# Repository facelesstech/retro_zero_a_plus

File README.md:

Blog post - https://facelesstech.wordpress.com/2019/10/12/arduboy-with-removable-flash-cart/
Youtube - https://youtu.be/ISeOyM-dqaA

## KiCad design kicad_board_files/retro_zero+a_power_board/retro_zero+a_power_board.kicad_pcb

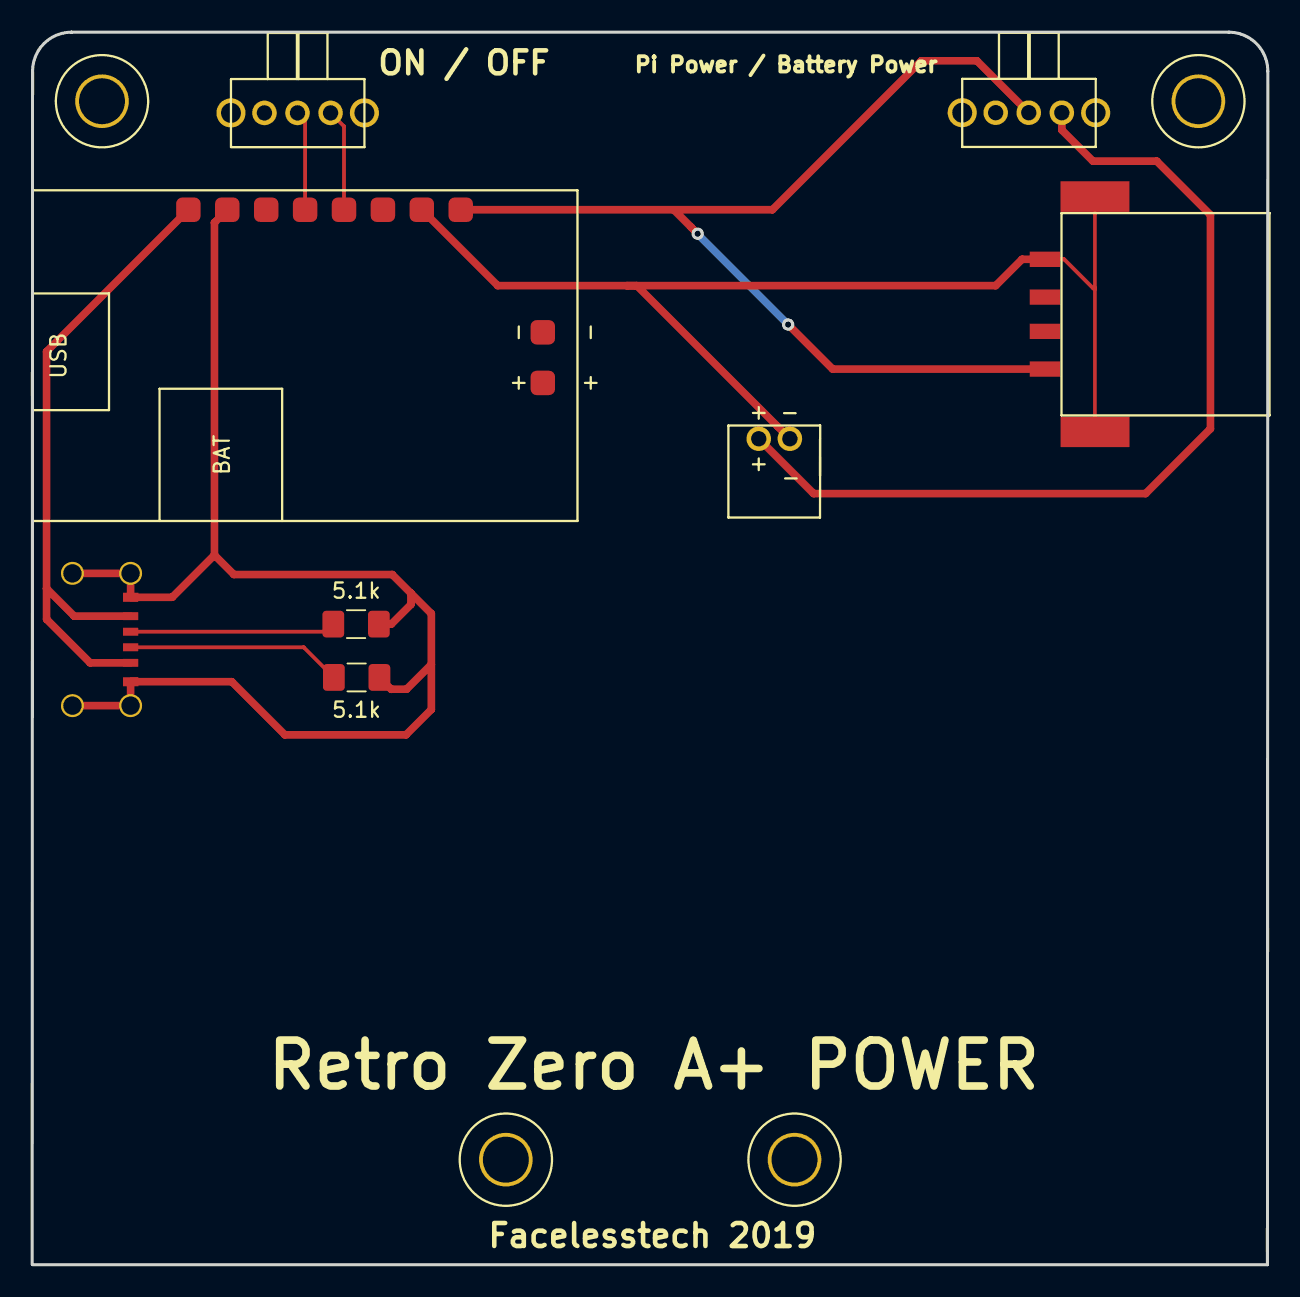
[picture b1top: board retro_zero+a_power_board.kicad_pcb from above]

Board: 2 copper layers, 80.7 x 80.5 mm, 12 parts (0 on the bottom side), 9 nets.

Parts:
5.1k, 5.1k#2: R; R_1206_3216Metric_Pad1.42x1.75mm_HandSolder
J1: USB_A; female_usb_custom_smd
SW1, SW2: SW_Push_SPDT; 3_pin_switch__right_angle_custom
U1: battery_custom; jst_2pin_right_angle
U2: power_boost_500; power_boost_500_smd
U3: usb_c_6pin; USB_C_6PIN_custom
U5, U6, U7, U8: m3_standsoffs; m3_hole_custom

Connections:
unnamed: J1.1, SW1.2, U2.8
unnamed: J1.4, J1.5, U1.1, U2.7
unnamed: 5.1k.1, 5.1k#2.1, U2.2, U3.1
unnamed: 5.1k.2, U3.3
unnamed: 5.1k#2.2, U3.4
unnamed: SW1.3, U1.2
unnamed: SW2.2, U2.4
unnamed: SW2.3, U2.5
unnamed: U2.1, U3.2

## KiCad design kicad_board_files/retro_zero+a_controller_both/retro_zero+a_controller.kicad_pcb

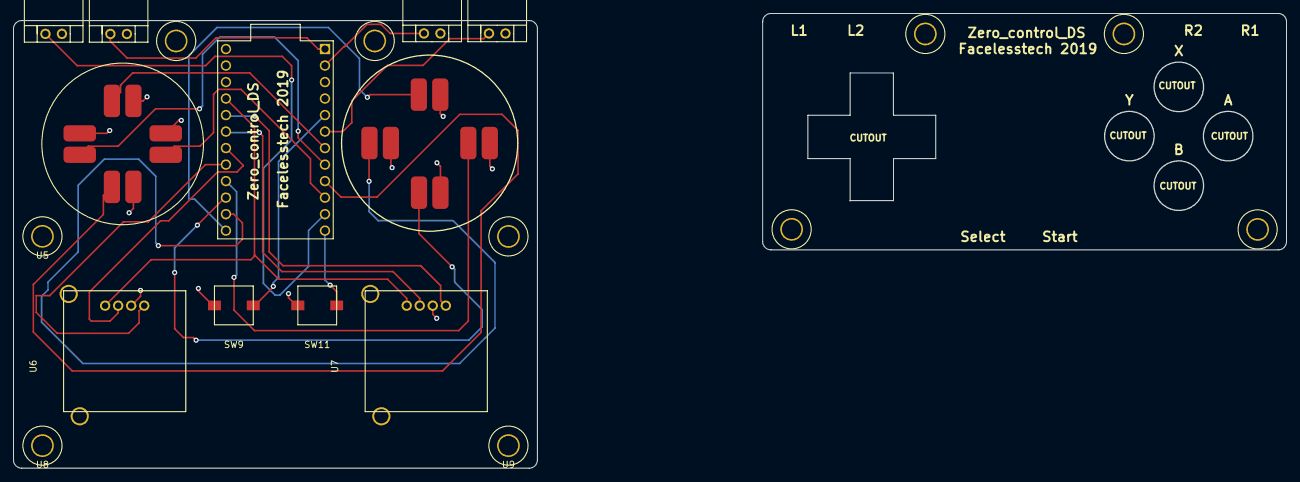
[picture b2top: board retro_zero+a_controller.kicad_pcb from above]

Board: 2 copper layers, 195.8 x 69.9 mm, 27 parts (1 on the bottom side), 24 nets.

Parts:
SW1, SW2, SW3, SW4, SW5, SW6, SW7, SW8: SW_Push; gbc_buttons_custom
SW9, SW11: SW_Push; smd_soft_custom
SW10, SW12, SW13, SW14: SW_Push; right_angle_2_pin
U1: ProMicro
U2, U2#2, U3, U3#2, U4, U4#2, U5, U5#2, U8, U9: m3_standsoffs; m3_hole_custom
U6, U7: psp_under_pad_custom

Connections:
unnamed: SW1.1, U1.8
unnamed: SW1.2, SW2.2, SW3.2, SW4.2, SW5.2, SW6.2, SW7.2, SW8.2, SW9.2, SW10.2, SW11.2, SW12.2, SW13.2, SW14.2, U1.23, U6.2, U7.2
unnamed: SW2.1, U1.10
unnamed: SW3.1, U1.7
unnamed: SW4.1, U1.9
unnamed: SW5.1, U1.13
unnamed: SW6.1, U1.15
unnamed: SW7.1, U1.14
unnamed: SW8.1, U1.16
unnamed: SW9.1, U1.5
unnamed: SW10.1, U1.11
unnamed: SW11.1, U1.12
unnamed: SW12.1, U1.6
unnamed: SW13.1, U1.1
unnamed: SW14.1, U1.2
unnamed: U1.17, U6.1
unnamed: U1.18, U6.3
unnamed: U1.19, U7.3
unnamed: U1.20, U7.1
unnamed: U1.21, U6.4, U7.4
unnamed: U2.1, U2#2.1
unnamed: U3.1, U3#2.1
unnamed: U4.1, U4#2.1
unnamed: U5.1, U5#2.1

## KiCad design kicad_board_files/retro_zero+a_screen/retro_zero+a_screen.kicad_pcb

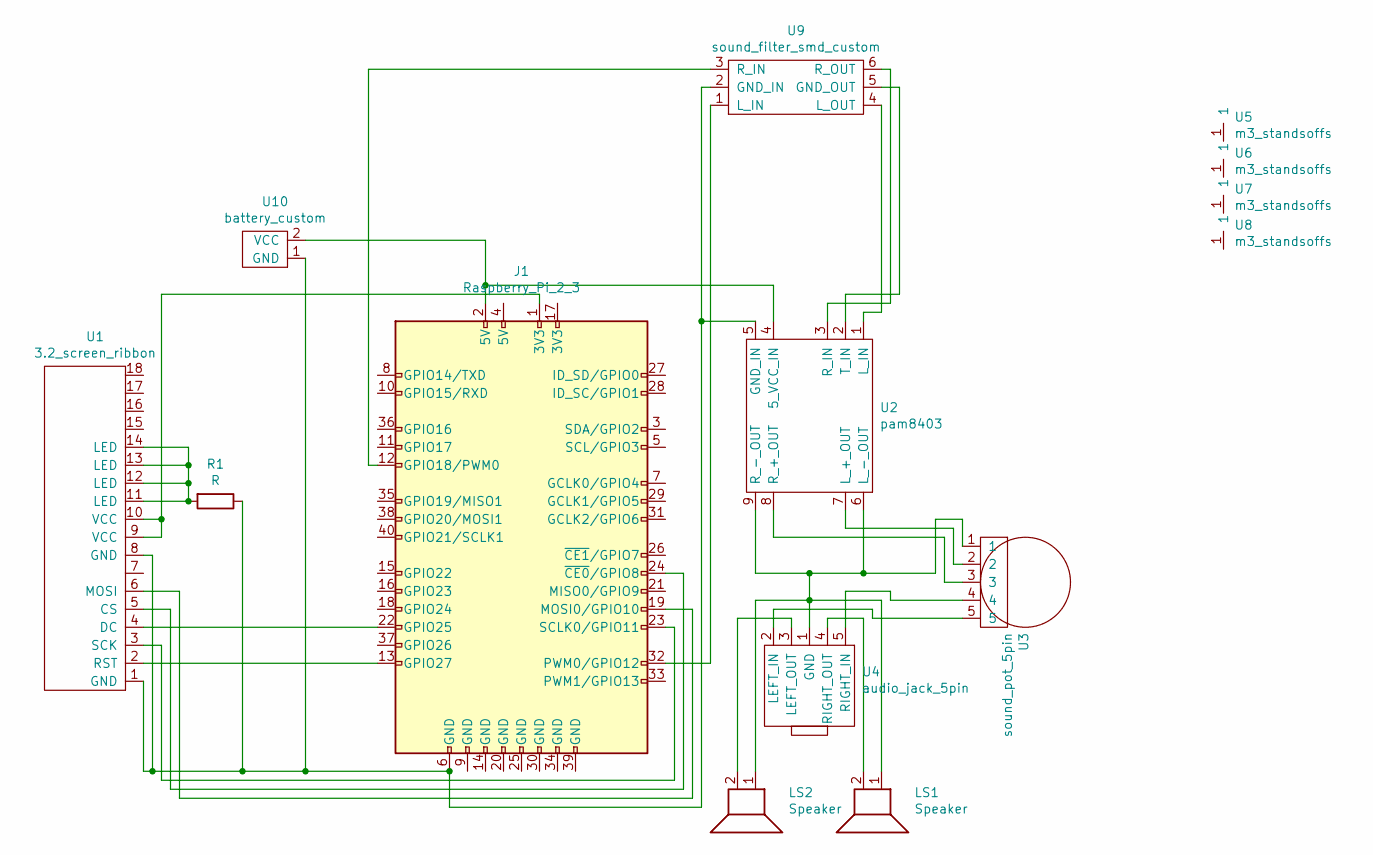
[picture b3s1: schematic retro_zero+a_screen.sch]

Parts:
J1: Raspberry_Pi_2_3; raspberry_pi_a+_gpio_smd_socket_outline_custom
LS1, LS2: Speaker; square_smd_speaker_custom
R1: R; R_1206_3216Metric
U1: 3.2_screen_ribbon; 3.2_screen_ribbon_breakout
U2: pam8403; PAM8403_custom_smd
U3: sound_pot_5pin; GBC_pot_custom
U4: audio_jack_5pin; 5_pin_3.5_jack
U5, U6, U7, U8: m3_standsoffs; m3_hole_custom
U9: sound_filter_smd_custom; Sound_filter_custom_smd
U10: battery_custom; jst_2pin_right_angle

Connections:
unnamed: J1.1 (3V3), U1.9 (VCC), U1.10 (VCC)
unnamed: J1.2 (5V), U2.4 (5_VCC_IN), U10.2 (VCC)
unnamed: J1.6 (GND), R1.1, U1.1 (GND), U1.8 (GND), U2.5 (GND_IN), U9.2 (GND_IN), U10.1 (GND)
unnamed: J1.12 (GPIO18/PWM0), U9.3 (R_IN)
unnamed: J1.13 (GPIO27), U1.2 (RST)
unnamed: J1.19 (MOSI0/GPIO10), U1.6 (MOSI)
unnamed: J1.22 (GPIO25), U1.4 (DC)
unnamed: J1.23 (SCLK0/GPIO11), U1.3 (SCK)
unnamed: J1.24 (~CE0~/GPIO8), U1.5 (CS)
unnamed: J1.32 (PWM0/GPIO12), U9.1 (L_IN)
unnamed: LS1.1, LS2.1, U2.6 (L_-_OUT), U2.9 (R_-_OUT), U3.1, U4.1 (GND)
unnamed: LS1.2, U4.4 (RIGHT_OUT)
unnamed: LS2.2, U4.3 (LEFT_OUT)
unnamed: R1.2, U1.11 (LED), U1.12 (LED), U1.13 (LED), U1.14 (LED)
unnamed: U2.1 (L_IN), U9.4 (L_OUT)
unnamed: U2.2 (T_IN), U9.5 (GND_OUT)
unnamed: U2.3 (R_IN), U9.6 (R_OUT)
unnamed: U2.7 (L_+_OUT), U3.2
unnamed: U2.8 (R_+_OUT), U3.3
unnamed: U3.4, U4.5 (RIGHT_IN)
unnamed: U3.5, U4.2 (LEFT_IN)

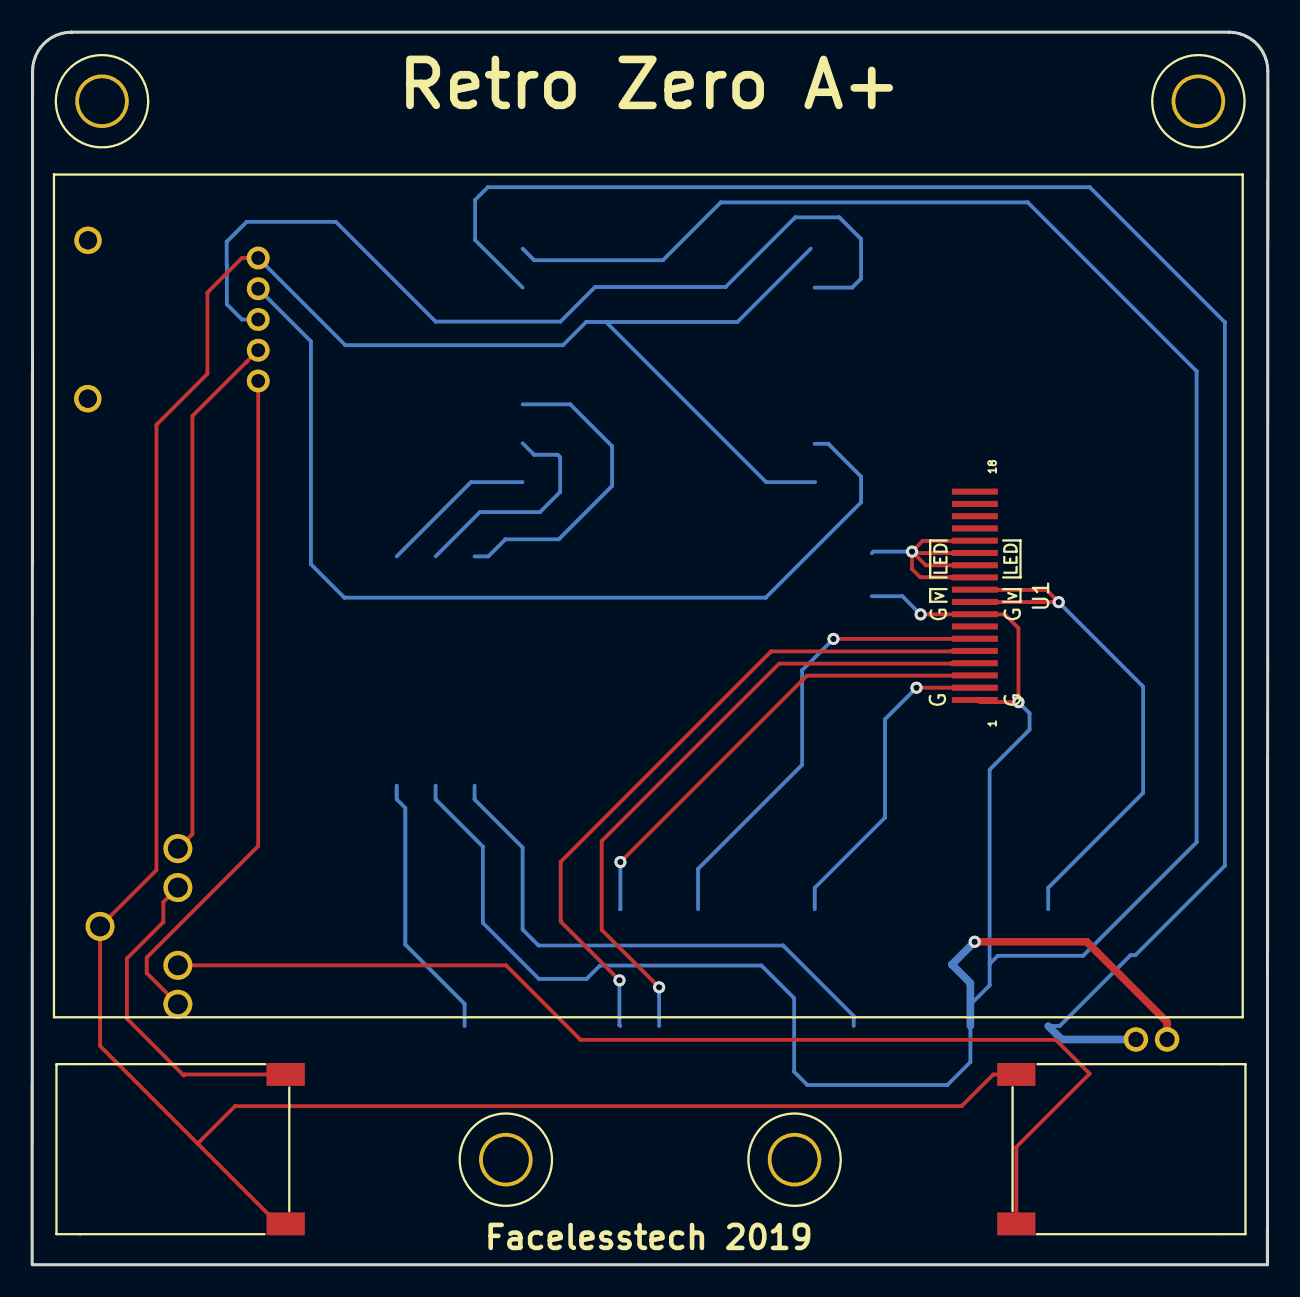
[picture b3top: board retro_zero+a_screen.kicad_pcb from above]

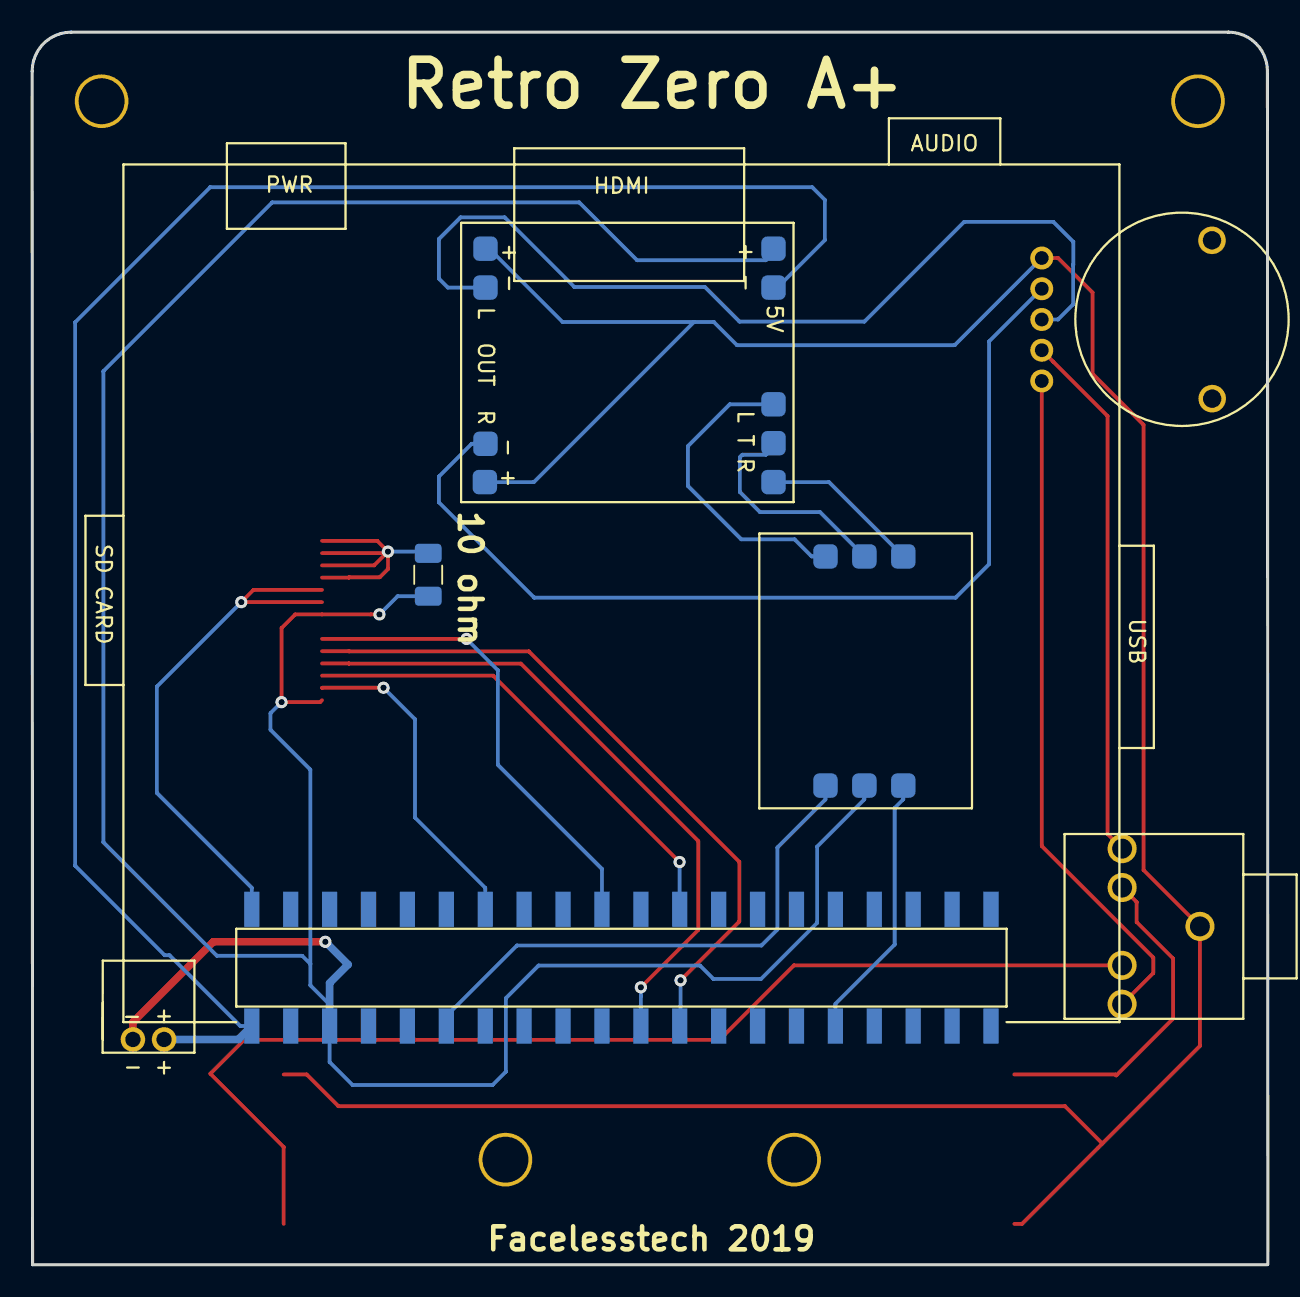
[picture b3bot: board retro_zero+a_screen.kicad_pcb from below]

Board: 2 copper layers, 80.7 x 80.5 mm, 14 parts (7 on the bottom side), 21 nets.

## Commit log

2019-07-09 tiny usb board files
2019-10-10 board files
2019-10-20 arduino controller board code
2020-02-27 added links to readme
